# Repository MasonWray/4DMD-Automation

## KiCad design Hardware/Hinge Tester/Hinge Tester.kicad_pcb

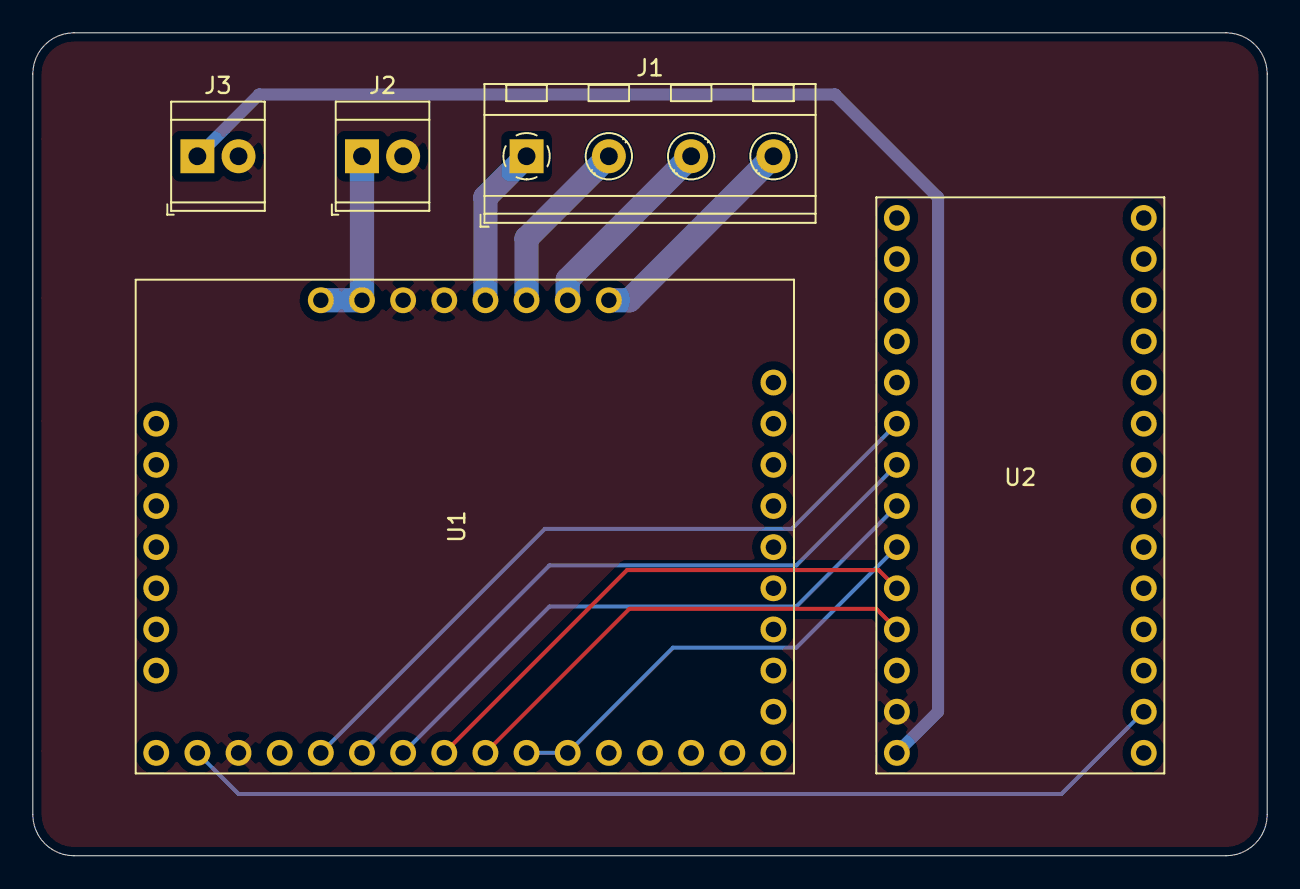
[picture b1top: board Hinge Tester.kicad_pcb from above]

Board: 2 copper layers, 76.2 x 50.8 mm, 5 parts (0 on the bottom side), 14 nets.

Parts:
J1: Conn_01x04_Female; TerminalBlock_RND_205-00234_1x04_P5.08mm_Horizontal
J2, J3: Conn_01x02_Female; TerminalBlock_TE_282834-2_1x02_P2.54mm_Horizontal
U1: TB67S128FTG
U2: Adafruit_ItsyBitsy_M4_Express; Adafruit_ItsyBitsy_M4

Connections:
+3V3: U1.24, U2.2
+5V: J3.1, U2.33
+24V: J2.1, U1.33, U1.34
DIR: U1.18, U2.29
EN: U1.15, U1.16, U2.28
GND: J2.2, J3.2, U1.23, U1.35, U1.36, U2.32
M0: U1.21, U2.25
M1: U1.20, U2.26
M2: U1.19, U2.27
unnamed: J1.1, U1.37
unnamed: J1.2, U1.38
unnamed: J1.3, U1.39
unnamed: J1.4, U1.40
STEP: U1.17, U2.30

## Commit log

2022-10-27 Add firmware projects
2022-10-27 Add LED status indicator control
2022-10-27 Read/Write config file
2022-11-02 Sweep stepper
2022-11-02 Create controller board schematic
2022-11-02 Add terminal block footprints
2022-11-02 Add footprints to schematic
2022-11-02 Add rough board layout
2022-11-02 Improve page layout
2022-11-02 Added PDF docs
2022-11-03 Implement basic stepper sweep
2023-01-01 Add schematic
2023-01-01 Add startup delay (wait for serial)
2023-01-01 Enter REPL when serial is connected
2023-01-01 Parse steps command
2023-01-01 update config settings via serial commands
2023-01-01 Save config to flash
2023-01-01 Load config on startup and view
2023-01-01 Add help command
2023-01-17 Echo command input
